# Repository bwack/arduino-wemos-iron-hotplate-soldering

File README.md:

# arduino-wemos-iron-hotplate-soldering

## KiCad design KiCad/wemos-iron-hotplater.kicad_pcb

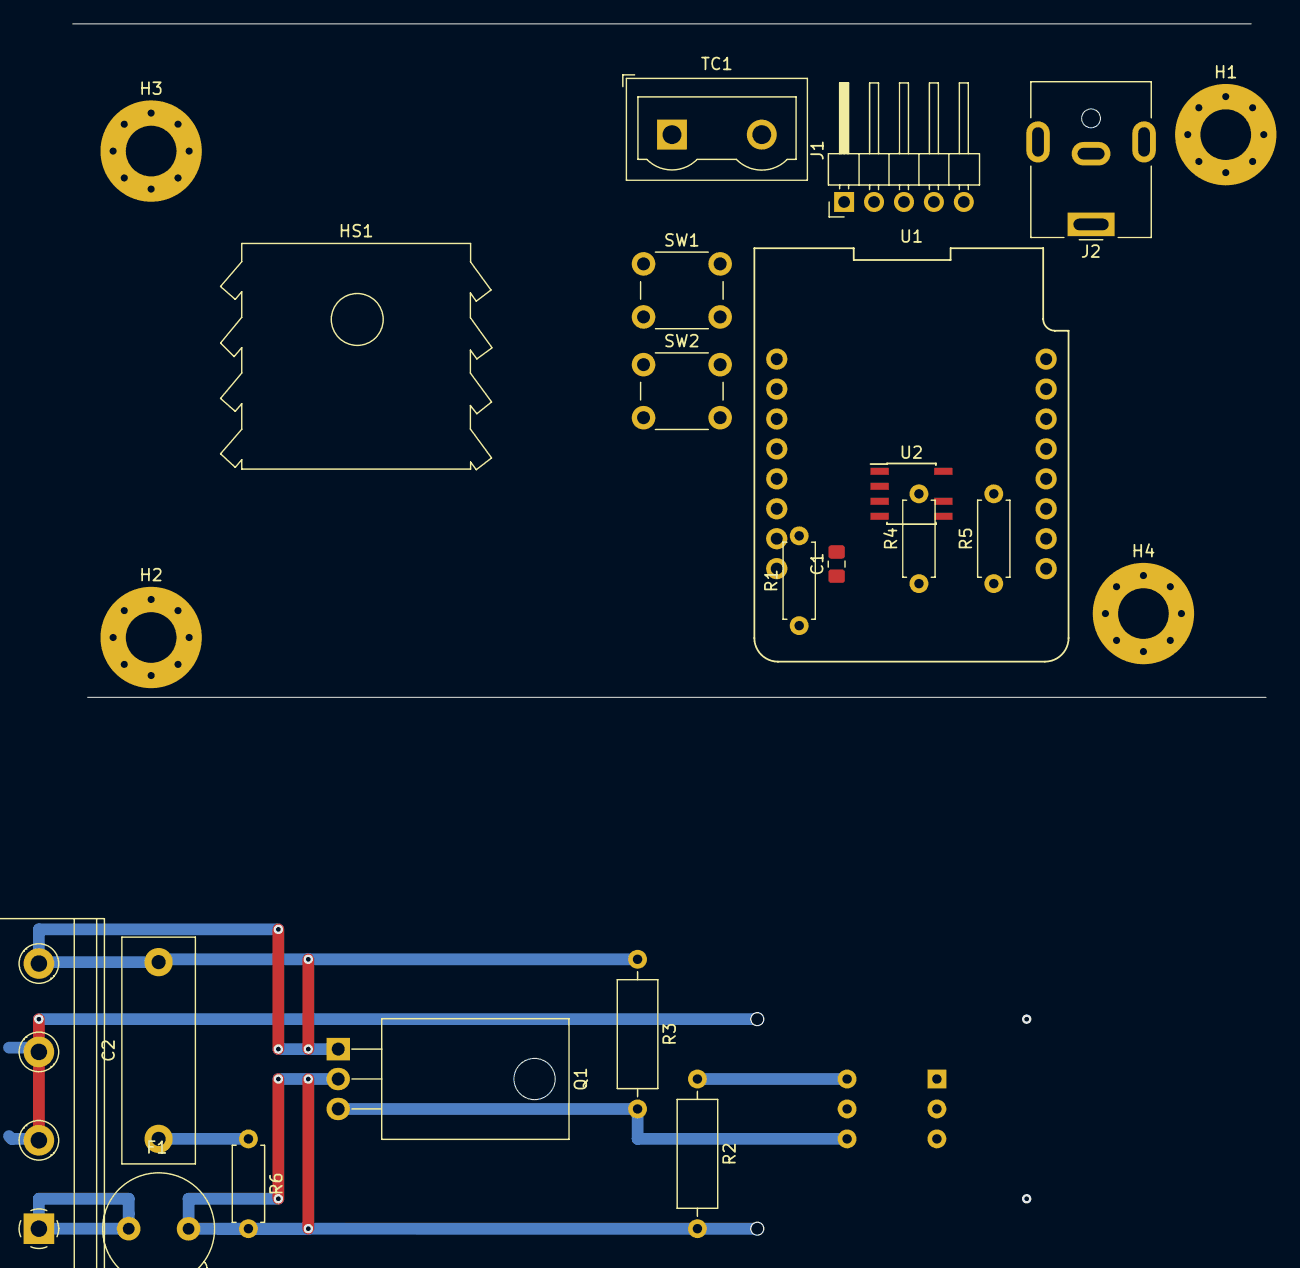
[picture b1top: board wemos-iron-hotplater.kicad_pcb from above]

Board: 2 copper layers, 24 parts (1 on the bottom side), 21 nets.

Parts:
C1: 100nF; C_0805_2012Metric_Pad1.15x1.40mm_HandSolder
C2: 10n; C_Rect_L19.0mm_W6.0mm_P15.00mm_MKS4
F1: Fuse; Fuseholder_TR5_Littelfuse_No560_No460
H1, H2, H3, H4: MountingHole_Pad; MountingHole_4.3mm_M4_Pad_Via
HS1: Heatsink; Heatsink_Aavid-TV5G_TO220_Horizontal
J1: Conn_01x05; PinHeader_1x05_P2.54mm_Horizontal
J2: Barrel_Jack; BarrelJack_CUI_PJ-063AH_Horizontal
J3: Screw_Terminal_01x04; TerminalBlock_MetzConnect_Type175_RT02704HBLC_1x04_P7.50mm_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
Q1: BT139-600; TO-220-3_Horizontal_TabDown
R1, R4, R5: 360; R_Axial_DIN0207_L6.3mm_D2.5mm_P7.62mm_Horizontal
R2: 360; R_Axial_DIN0309_L9.0mm_D3.2mm_P12.70mm_Horizontal
R3: 330; R_Axial_DIN0309_L9.0mm_D3.2mm_P12.70mm_Horizontal
R6: 47; R_Axial_DIN0207_L6.3mm_D2.5mm_P7.62mm_Horizontal
SW1, SW2: SW_Push; SW_PUSH_6mm
TC1: Thermocouple_ALT; TerminalBlock_Wuerth_691311400102_P7.62mm
U1: WeMos_D1_mini; wemos-d1-mini-connectors-only
U2: MAX6675; SOIC-8-N7_3.9x4.9mm_P1.27mm
U3: MOC3041M; DIP-6_W7.62mm

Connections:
+3V3: C1.1, R4.2, R5.2, U1.8, U2.4
+5V: J1.4, J2.1, U1.9
/CS_DISPL: J1.3, U1.7
/CS_THERM: U1.6, U2.6
/HOT: F1.1, J3.1
/MISO: J1.2, U1.5
/NEUTRAL: J3.2, J3.3
/SCK: J1.1, U1.4, U2.5
Earth: H1.1, H2.1, H3.1, H4.1
GND: C1.2, J1.5, J2.2, SW1.2, SW2.2, U1.10, U2.1, U3.2
unnamed: C2.1, R6.1
unnamed: C2.2, J3.4, Q1.1, R3.1
unnamed: F1.2, Q1.2, R2.2, R6.2
unnamed: Q1.3, R3.2, U3.4
unnamed: R1.1, U3.1
unnamed: R1.2, U1.14
unnamed: R2.1, U3.6
unnamed: R4.1, SW1.1, U1.11
unnamed: R5.1, SW2.1, U1.12
unnamed: TC1.1, U2.2
unnamed: TC1.2, U2.3

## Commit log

2020-12-05 added pdf
